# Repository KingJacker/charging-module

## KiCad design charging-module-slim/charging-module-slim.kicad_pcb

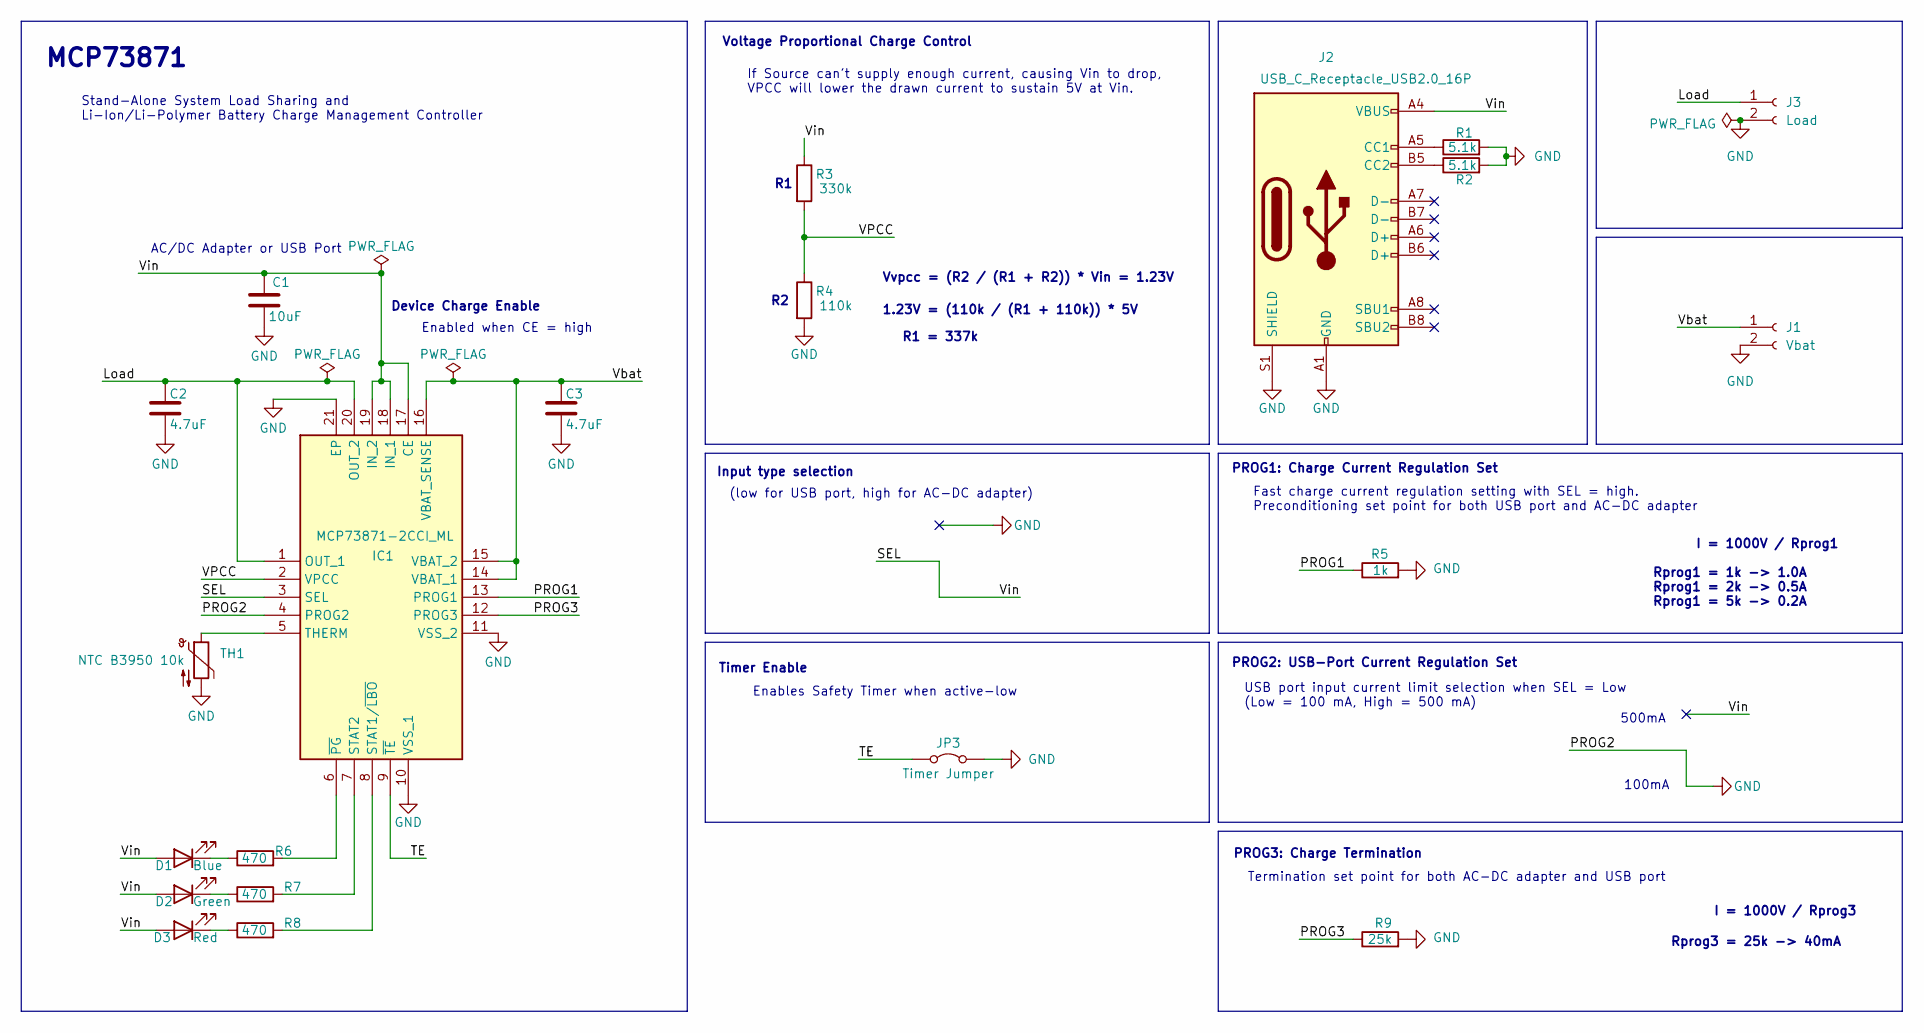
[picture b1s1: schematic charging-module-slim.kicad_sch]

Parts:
C1: 10uF; C_0805_2012Metric_Pad1.18x1.45mm_HandSolder
C2, C3: 4.7uF; C_0805_2012Metric_Pad1.18x1.45mm_HandSolder
D1: Blue; LED_0805_2012Metric_Pad1.15x1.40mm_HandSolder
D2: Green; LED_0805_2012Metric_Pad1.15x1.40mm_HandSolder
D3: Red; LED_0805_2012Metric_Pad1.15x1.40mm_HandSolder
IC1: MCP73871-2CCI_ML; QFN50P400X400X100-21N-D; Mouser Part Number 579-MCP73871-2CCI/ML
J1: Vbat; PinSocket_1x02_P2.00mm_Vertical
J2: USB_C_Receptacle_USB2.0_16P; USB_C_Receptacle_HRO_TYPE-C-31-M-12
J3: Load; PinSocket_1x02_P2.00mm_Vertical
JP3: Timer Jumper; SolderJumper-2_P1.3mm_Bridged_RoundedPad1.0x1.5mm
R1, R2: 5.1k; R_0805_2012Metric_Pad1.20x1.40mm_HandSolder
R3: 330k; R_0805_2012Metric_Pad1.20x1.40mm_HandSolder
R4: 110k; R_0805_2012Metric_Pad1.20x1.40mm_HandSolder
R5: 1k; R_0805_2012Metric_Pad1.20x1.40mm_HandSolder
R6, R7, R8: 470; R_0805_2012Metric_Pad1.20x1.40mm_HandSolder
R9: 25k; R_0805_2012Metric_Pad1.20x1.40mm_HandSolder
TH1: NTC B3950 10k; PinSocket_1x02_P2.00mm_Vertical

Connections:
/Load: C2.1, IC1.1 (OUT_1), IC1.20 (OUT_2), J3.1
/PROG1: IC1.13 (PROG1), R5.1
/PROG3: IC1.12 (PROG3), R9.1
/SEL: C1.1, D1.2 (A), D2.2 (A), D3.2 (A), IC1.3 (SEL), IC1.17 (CE), IC1.18 (IN_1), IC1.19 (IN_2), J2.A4 (VBUS), J2.A9 (VBUS), J2.B4 (VBUS), J2.B9 (VBUS), R3.1
/TE: IC1.9 (~TE), JP3.1 (A)
/VPCC: IC1.2 (VPCC), R3.2, R4.1
/Vbat: C3.1, IC1.14 (VBAT_1), IC1.15 (VBAT_2), IC1.16 (VBAT_SENSE), J1.1
GND: C1.2, C2.2, C3.2, IC1.4 (PROG2), IC1.10 (VSS_1), IC1.11 (VSS_2), IC1.21 (EP), J1.2, J2.A1 (GND), J2.A12 (GND), J2.B1 (GND), J2.B12 (GND), J2.S1 (SHIELD), J3.2, JP3.2 (B), R1.2, R2.2, R4.2, R5.2, R9.2, TH1.2
unnamed: D1.1 (K), R6.1
unnamed: D2.1 (K), R7.1
unnamed: D3.1 (K), R8.1
unnamed: IC1.8 (STAT1/~LBO), R8.2
unnamed: IC1.7 (STAT2), R7.2
unnamed: IC1.5 (THERM), TH1.1
unnamed: IC1.6 (~PG), R6.2
unnamed: J2.A5 (CC1), R1.1
unnamed: J2.B5 (CC2), R2.1

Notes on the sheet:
Vvpcc = (R2 / (R1 + R2)) * Vin = 1.23V
Stand-Alone System Load Sharing and Li-Ion/Li-Polymer Battery Charge Management Controller
Device Charge Enable
USB port input current limit selection when SEL = Low (Low = 100 mA, High = 500 mA)
AC/DC Adapter or USB Port
I = 1000V / Rprog1
PROG2: USB-Port Current Regulation Set
Enables Safety Timer when active-low
Fast charge current regulation setting with SEL = high. Preconditioning set point for both USB port and AC-DC adapter
MCP73871
Voltage Proportional Charge Control
Rprog1 = 1k -> 1.0A
500mA
If Source can't supply enough current, causing Vin to drop, VPCC will lower the drawn current to sustain 5V at Vin.
Rprog1 = 2k -> 0.5A
Enabled when CE = high
100mA
Termination set point for both AC-DC adapter and USB port
I = 1000V / Rprog3
Rprog1 = 5k -> 0.2A
PROG3: Charge Termination
1.23V = (110k / (R1 + 110k)) * 5V
Timer Enable
PROG1: Charge Current Regulation Set
(low for USB port, high for AC-DC adapter)
Input type selection
R1 = 337k
Rprog3 = 25k -> 40mA

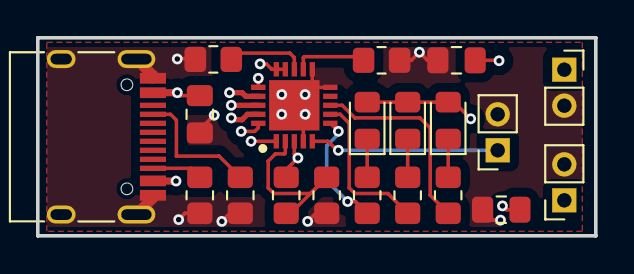
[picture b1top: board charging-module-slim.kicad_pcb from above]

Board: 4 copper layers, 31.0 x 11.0 mm, 20 parts (0 on the bottom side), 16 nets.

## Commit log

2025-08-18 files
2025-09-12 MCP73871 schematic
2025-09-12 removed overvoltage diode
2025-09-12 assigned footprints
2025-09-12 started on layout
2025-09-12 layout
2025-09-13 layout done
2025-09-13 layout slim
